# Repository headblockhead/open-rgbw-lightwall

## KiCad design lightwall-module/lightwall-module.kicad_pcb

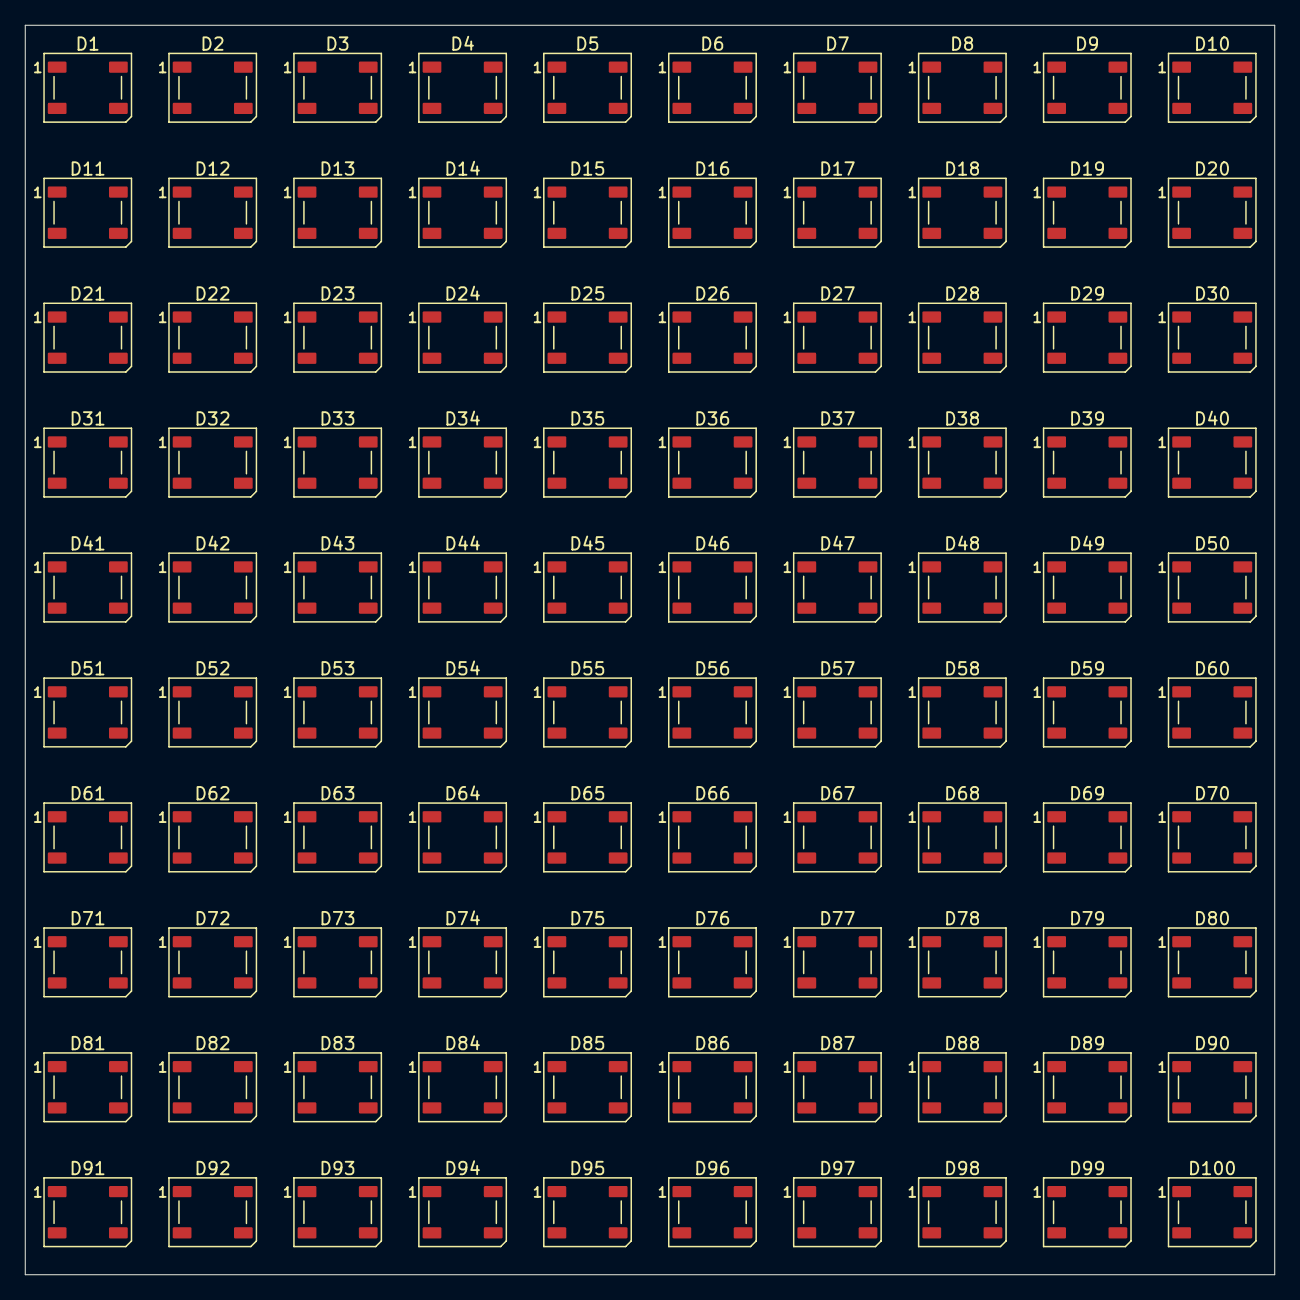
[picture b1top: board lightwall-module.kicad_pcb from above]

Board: 2 copper layers, 100.0 x 100.0 mm, 100 parts (0 on the bottom side), 4 nets, no tracks yet.

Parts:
D1, D2, D3, D4, D5, D6, D7, D8, D9, D10, D11, D12, D13, D14, D15, D16, D17, D18, D19, D20, D21, D22, D23, D24, D25, D26, D27, D28, D29, D30, D31, D32, D33, D34, D35, D36, D37, D38, D39, D40, D41, D42, D43, D44, D45, D46, D47, D48, D49, D50, D51, D52, D53, D54, D55, D56, D57, D58, D59, D60, D61, D62, D63, D64, D65, D66, D67, D68, D69, D70, D71, D72, D73, D74, D75, D76, D77, D78, D79, D80, D81, D82, D83, D84, D85, D86, D87, D88, D89, D90, D91, D92, D93, D94, D95, D96, D97, D98, D99, D100: WS2812B; LED_WS2812B_PLCC4_5.0x5.0mm_P3.2mm

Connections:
+5V: D1.1 (VDD), D2.1 (VDD), D3.1 (VDD), D4.1 (VDD), D5.1 (VDD), D6.1 (VDD), D7.1 (VDD), D8.1 (VDD), D9.1 (VDD), D10.1 (VDD), D11.1 (VDD), D12.1 (VDD), D13.1 (VDD), D14.1 (VDD), D15.1 (VDD), D16.1 (VDD), D17.1 (VDD), D18.1 (VDD), D19.1 (VDD), D20.1 (VDD), D21.1 (VDD), D22.1 (VDD), D23.1 (VDD), D24.1 (VDD), D25.1 (VDD), D26.1 (VDD), D27.1 (VDD), D28.1 (VDD), D29.1 (VDD), D30.1 (VDD), D31.1 (VDD), D32.1 (VDD), D33.1 (VDD), D34.1 (VDD), D35.1 (VDD), D36.1 (VDD), D37.1 (VDD), D38.1 (VDD), D39.1 (VDD), D40.1 (VDD), D41.1 (VDD), D42.1 (VDD), D43.1 (VDD), D44.1 (VDD), D45.1 (VDD), D46.1 (VDD), D47.1 (VDD), D48.1 (VDD), D49.1 (VDD), D50.1 (VDD), D51.1 (VDD), D52.1 (VDD), D53.1 (VDD), D54.1 (VDD), D55.1 (VDD), D56.1 (VDD), D57.1 (VDD), D58.1 (VDD), D59.1 (VDD), D60.1 (VDD), D61.1 (VDD), D62.1 (VDD), D63.1 (VDD), D64.1 (VDD), D65.1 (VDD), D66.1 (VDD), D67.1 (VDD), D68.1 (VDD), D69.1 (VDD), D70.1 (VDD), D71.1 (VDD), D72.1 (VDD), D73.1 (VDD), D74.1 (VDD), D75.1 (VDD), D76.1 (VDD), D77.1 (VDD), D78.1 (VDD), D79.1 (VDD), D80.1 (VDD), D81.1 (VDD), D82.1 (VDD), D83.1 (VDD), D84.1 (VDD), D85.1 (VDD), D86.1 (VDD), D87.1 (VDD), D88.1 (VDD), D89.1 (VDD), D90.1 (VDD), D91.1 (VDD), D92.1 (VDD), D93.1 (VDD), D94.1 (VDD), D95.1 (VDD), D96.1 (VDD), D97.1 (VDD), D98.1 (VDD), D99.1 (VDD), D100.1 (VDD)
/LED Array/LED_INPUT: D1.4 (DIN), D2.4 (DIN), D3.4 (DIN), D4.4 (DIN), D5.4 (DIN), D6.4 (DIN), D7.4 (DIN), D8.4 (DIN), D9.4 (DIN), D10.4 (DIN), D11.4 (DIN), D12.4 (DIN), D13.4 (DIN), D14.4 (DIN), D15.4 (DIN), D16.4 (DIN), D17.4 (DIN), D18.4 (DIN), D19.4 (DIN), D20.4 (DIN), D21.4 (DIN), D22.4 (DIN), D23.4 (DIN), D24.4 (DIN), D25.4 (DIN), D26.4 (DIN), D27.4 (DIN), D28.4 (DIN), D29.4 (DIN), D30.4 (DIN), D31.4 (DIN), D32.4 (DIN), D33.4 (DIN), D34.4 (DIN), D35.4 (DIN), D36.4 (DIN), D37.4 (DIN), D38.4 (DIN), D39.4 (DIN), D40.4 (DIN), D41.4 (DIN), D42.4 (DIN), D43.4 (DIN), D44.4 (DIN), D45.4 (DIN), D46.4 (DIN), D47.4 (DIN), D48.4 (DIN), D49.4 (DIN), D50.4 (DIN), D51.4 (DIN), D52.4 (DIN), D53.4 (DIN), D54.4 (DIN), D55.4 (DIN), D56.4 (DIN), D57.4 (DIN), D58.4 (DIN), D59.4 (DIN), D60.4 (DIN), D61.4 (DIN), D62.4 (DIN), D63.4 (DIN), D64.4 (DIN), D65.4 (DIN), D66.4 (DIN), D67.4 (DIN), D68.4 (DIN), D69.4 (DIN), D70.4 (DIN), D71.4 (DIN), D72.4 (DIN), D73.4 (DIN), D74.4 (DIN), D75.4 (DIN), D76.4 (DIN), D77.4 (DIN), D78.4 (DIN), D79.4 (DIN), D80.4 (DIN), D81.4 (DIN), D82.4 (DIN), D83.4 (DIN), D84.4 (DIN), D85.4 (DIN), D86.4 (DIN), D87.4 (DIN), D88.4 (DIN), D89.4 (DIN), D90.4 (DIN), D91.4 (DIN), D92.4 (DIN), D93.4 (DIN), D94.4 (DIN), D95.4 (DIN), D96.4 (DIN), D97.4 (DIN), D98.4 (DIN), D99.4 (DIN), D100.4 (DIN)
GND: D1.3 (VSS), D2.3 (VSS), D3.3 (VSS), D4.3 (VSS), D5.3 (VSS), D6.3 (VSS), D7.3 (VSS), D8.3 (VSS), D9.3 (VSS), D10.3 (VSS), D11.3 (VSS), D12.3 (VSS), D13.3 (VSS), D14.3 (VSS), D15.3 (VSS), D16.3 (VSS), D17.3 (VSS), D18.3 (VSS), D19.3 (VSS), D20.3 (VSS), D21.3 (VSS), D22.3 (VSS), D23.3 (VSS), D24.3 (VSS), D25.3 (VSS), D26.3 (VSS), D27.3 (VSS), D28.3 (VSS), D29.3 (VSS), D30.3 (VSS), D31.3 (VSS), D32.3 (VSS), D33.3 (VSS), D34.3 (VSS), D35.3 (VSS), D36.3 (VSS), D37.3 (VSS), D38.3 (VSS), D39.3 (VSS), D40.3 (VSS), D41.3 (VSS), D42.3 (VSS), D43.3 (VSS), D44.3 (VSS), D45.3 (VSS), D46.3 (VSS), D47.3 (VSS), D48.3 (VSS), D49.3 (VSS), D50.3 (VSS), D51.3 (VSS), D52.3 (VSS), D53.3 (VSS), D54.3 (VSS), D55.3 (VSS), D56.3 (VSS), D57.3 (VSS), D58.3 (VSS), D59.3 (VSS), D60.3 (VSS), D61.3 (VSS), D62.3 (VSS), D63.3 (VSS), D64.3 (VSS), D65.3 (VSS), D66.3 (VSS), D67.3 (VSS), D68.3 (VSS), D69.3 (VSS), D70.3 (VSS), D71.3 (VSS), D72.3 (VSS), D73.3 (VSS), D74.3 (VSS), D75.3 (VSS), D76.3 (VSS), D77.3 (VSS), D78.3 (VSS), D79.3 (VSS), D80.3 (VSS), D81.3 (VSS), D82.3 (VSS), D83.3 (VSS), D84.3 (VSS), D85.3 (VSS), D86.3 (VSS), D87.3 (VSS), D88.3 (VSS), D89.3 (VSS), D90.3 (VSS), D91.3 (VSS), D92.3 (VSS), D93.3 (VSS), D94.3 (VSS), D95.3 (VSS), D96.3 (VSS), D97.3 (VSS), D98.3 (VSS), D99.3 (VSS), D100.3 (VSS)
unnamed: D1.2 (DOUT), D2.2 (DOUT), D3.2 (DOUT), D4.2 (DOUT), D5.2 (DOUT), D6.2 (DOUT), D7.2 (DOUT), D8.2 (DOUT), D9.2 (DOUT), D10.2 (DOUT), D11.2 (DOUT), D12.2 (DOUT), D13.2 (DOUT), D14.2 (DOUT), D15.2 (DOUT), D16.2 (DOUT), D17.2 (DOUT), D18.2 (DOUT), D19.2 (DOUT), D20.2 (DOUT), D21.2 (DOUT), D22.2 (DOUT), D23.2 (DOUT), D24.2 (DOUT), D25.2 (DOUT), D26.2 (DOUT), D27.2 (DOUT), D28.2 (DOUT), D29.2 (DOUT), D30.2 (DOUT), D31.2 (DOUT), D32.2 (DOUT), D33.2 (DOUT), D34.2 (DOUT), D35.2 (DOUT), D36.2 (DOUT), D37.2 (DOUT), D38.2 (DOUT), D39.2 (DOUT), D40.2 (DOUT), D41.2 (DOUT), D42.2 (DOUT), D43.2 (DOUT), D44.2 (DOUT), D45.2 (DOUT), D46.2 (DOUT), D47.2 (DOUT), D48.2 (DOUT), D49.2 (DOUT), D50.2 (DOUT), D51.2 (DOUT), D52.2 (DOUT), D53.2 (DOUT), D54.2 (DOUT), D55.2 (DOUT), D56.2 (DOUT), D57.2 (DOUT), D58.2 (DOUT), D59.2 (DOUT), D60.2 (DOUT), D61.2 (DOUT), D62.2 (DOUT), D63.2 (DOUT), D64.2 (DOUT), D65.2 (DOUT), D66.2 (DOUT), D67.2 (DOUT), D68.2 (DOUT), D69.2 (DOUT), D70.2 (DOUT), D71.2 (DOUT), D72.2 (DOUT), D73.2 (DOUT), D74.2 (DOUT), D75.2 (DOUT), D76.2 (DOUT), D77.2 (DOUT), D78.2 (DOUT), D79.2 (DOUT), D80.2 (DOUT), D81.2 (DOUT), D82.2 (DOUT), D83.2 (DOUT), D84.2 (DOUT), D85.2 (DOUT), D86.2 (DOUT), D87.2 (DOUT), D88.2 (DOUT), D89.2 (DOUT), D90.2 (DOUT), D91.2 (DOUT), D92.2 (DOUT), D93.2 (DOUT), D94.2 (DOUT), D95.2 (DOUT), D96.2 (DOUT), D97.2 (DOUT), D98.2 (DOUT), D99.2 (DOUT), D100.2 (DOUT)

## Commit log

2025-05-31 Create LICENSE
2025-06-11 2025-06-11
